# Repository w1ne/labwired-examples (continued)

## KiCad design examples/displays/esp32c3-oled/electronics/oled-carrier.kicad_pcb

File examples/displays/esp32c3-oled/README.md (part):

# ESP32-C3 OLED device — Rev A candidate 3

This package contains a USB-powered OLED counter, its routed carrier PCB, firmware, enclosure CAD, assembly instructions and verification evidence. A Seeed XIAO ESP32C3 drives an Adafruit 326 STEMMA QT display. The counter starts at **19:00:00 after every reset** and advances once per second. It has no real-time clock, time-setting control or saved time.

**Status: engineering assembly candidate.** The corrected model retains the native PCB populated side at +Z and uses world Y = −editor Y. All **12/12** fit and registration checks pass. All **18 native drilled pads** match their STEP axes with zero XY error. The glass/support clearance remains **1.277 mm**, with **0.85 mm** support arms and the unchanged **0.8 mm** minimum-wall gate. Both printed parts pass DFM and closed-mesh checks; all **41/41** assembly STEP solids are valid. A fresh independent check passes **39 ordered geometric stages** for all 41 source parts and all 13 helper controls. Hosted assembly-path acceptance and physical qualification remain open. No physical prototype has been built.

The previous source reconstructed the populated assembly in the PCB editor's downward-Y frame. Rotating only the bare substrate hid that reflection. Candidate 3 corrects the primitive geometry, connector frames, print orientations and exported files. The earlier candidate releases remain immutable. Studio revision 3 now stores this corrected source and its original native STEP asset. Its ready mesh is bound to the exact source, asset manifest and deployed producer in the [saved-revision receipt](cad/verification/studio-current/revision.json).

[Open the canonical Lab](https://app.labwired.com/?lab=esp32c3-oled-lab) · [Current Studio revision 3](https://app.kernelcad.com/p/t_IaE1EE?version=3) · [Track remaining work](https://github.com/w1ne/labwired/issues/3550)

The canonical Lab integration is delivered by the associated platform change. Until that change deploys, the public Lab can still show the previous Super Mini starter. This repository and the release files identify the candidate independently of deployment.

## Package contents

| File or folder | Use |
| --- | --- |
| [bom.csv](bom.csv) | Complete electronics and enclosure BOM, with scoped assembly references and quantities |
| [electronics/oled-carrier.kicad_pro](electronics/oled-carrier.kicad_pro) | Editable KiCad 10 project; keep the entire `electronics/` folder with its rules and libraries |
| [manufacturing/oled-carrier-fabrication.zip](manufacturing/oled-carrier-fabrication.zip) | Gerbers, plated/non-plated drills, drill maps and fabrication settings |
| [manufacturing/oled-carrier-schematic.pdf](manufacturing/oled-carrier-schematic.pdf) | Readable schematic |
| [firmware/platformio.ini](firmware/platformio.ini) | Pinned XIAO build and separate address-scanner environment |
| [firmware/release-manifest.json](firmware/release-manifest.json) | Exact public ELF, merged flash, startup snapshot and ROM identities |
| [labwired/circuit.json](labwired/circuit.json) | The actual functional starter diagram exported from the platform implementation |
| [cad/esp32c3-oled-enclosure.kcad.ts](cad/esp32c3-oled-enclosure.kcad.ts) | Editable, parameterized KernelCAD source |
| [cad/exports/](cad/exports/) | Assembly STEP and separate base/lid STEP, STL and 3MF files |
| [cad/assembly.txt](cad/assembly.txt) | Print orientation, hardware stack, assembly sequence and fit checks |
| [release-manifest.json](release-manifest.json) | Package identity and file integrity manifest |
| [verification/](verification/) | Observed firmware results, build provenance and reproducible checks |

The complete package includes the `.kicad_dru` fastener keepouts, local symbol/footprint libraries and mechanical component assets. The Lab's native viewer downloads the `.kicad_pcb`, `.kicad_sch` and `.kicad_pro` for inspection; use the complete package for editing or fabrication.

## Electrical design

The carrier is **70 × 45 × 1.6 mm**, with two copper layers and four 2.9 mm non-plated mounting holes. It contains two XIAO sockets, a JST SH cable connector and two 4.7 kΩ pull-ups. The XIAO and OLED are purchased modules; their internal boards are not part of the carrier Gerbers.

| Signal | Controller | Carrier connector | Display |
| --- | --- | --- | --- |
| SDA | D2 / GPIO4, J2.3 | J1.3 | STEMMA QT SDA |
| SCL | D3 / GPIO5, J2.4 | J1.4 | STEMMA QT SCL |
| Power | 3V3, J3.5 | J1.2 | STEMMA QT VCC |
| Ground | GND, J3.6 | J1.1 | STEMMA QT GND |

GPIO4/5 are explicit firmware assignments. The XIAO's usual D4/D5 I²C labels refer to different GPIOs. Use the table above.

Use the **Adafruit 326 STEMMA QT revision**. Close **SJ3 / ADDR** to select `0x3C`; its open/default address is `0x3D`. Keep the factory I²C jumpers SJ1/SJ2 closed. Leave the optional eight-pin JP2 header unpopulated. Its physical order is SDA, SCL, DC/SA0, RST, CS, regulated 3.3 V output, Vin and GND.

Use the specified **Samtec BHS-107-G-A / HSS-107-G-2 round-pin pair**. The module tails are 0.46 mm in diameter and fit the XIAO's native 0.85 mm holes. A 0.635 mm square post has a 0.898 mm diagonal and does not fit that hole specification. The nominal mated board gap is 9.77 mm. Substituting a generic header changes both fit and enclosure height.

USB supplies the device. Battery pads and the carrier's VBUS socket contact are unused. The demo does not enable Wi-Fi or Bluetooth; its supplied antenna remains separate. Install the antenna before using firmware that enables RF.

The Lab diagram represents the **MCU/display functional connections**. The native carrier and complete BOM also contain sockets, connectors, pull-ups and mounting features. The preserve import of the carrier is an identity/geometry result and has no runnable MCU model. The firmware tests do not simulate all carrier copper, cable parasitics, analog power or mechanical fit.

## Build and flash

Use PlatformIO Core **6.2.0**. The project pins `espressif32@7.0.1`, the official `seeed_xiao_esp32c3` board and Arduino. Run these commands from this directory:

```sh
pio run -d firmware -e clock
pio run -d firmware -e i2c_scan
```

Both environments were built successfully. The tested clock application uses **271,678 bytes of flash** and **15,140 bytes of RAM** in this toolchain. The unchanged workshop sketch is mirrored from core commit `941a6c5caf0c53b66aa5af9290e5ecba5972ec72`; [source-provenance.json](firmware/source-provenance.json) records its path and SHA256.

For initial assembly, connect a USB-C **data** cable with the lid removed. Select the actual serial port when more than one board is connected:

```sh
pio run -d firmware -e i2c_scan -t upload --upload-port /dev/ttyACM0
pio device monitor -d firmware -e i2c_scan --port /dev/ttyACM0
```

The scanner must report `I2C_ACK 0x3C`. Stop the monitor, then upload the clock:

```sh
pio run -d firmware -e clock -t upload --upload-port /dev/ttyACM0
pio device monitor -d firmware -e clock --port /dev/ttyACM0
```

Confirm visible changes and serial lines `WORKSHOP_TICK 19:00:00`, then `WORKSHOP_TICK 19:00:01`. If automatic USB download entry is unavailable, hold BOOT, press and release RESET, then release BOOT and retry upload. Keep both buttons accessible until bring-up is complete.

The public runtime is [firmware-demos-v19](https://github.com/w1ne/labwired-core/releases/tag/firmware-demos-v19). Its ELF, merged flash and startup snapshot are a matched set. The startup snapshot was captured through real ROM boot from those exact bytes. The separate package build uses the same sketch and has a different ELF hash. Project paths can change ELF bytes. No byte-identical rebuild claim is made.

[verification/reproduce.txt](verification/reproduce.txt) downloads and checks the public runtime and runs the existing LabWired CLI against the packaged configuration. It also describes the standalone-build ROM-boot check. The package does not add a simulator or a custom device model.

## Assemble the candidate

1. Follow [electronics/assembly-notes.txt](electronics/assembly-notes.txt). Populate the five carrier components, fit the round-pin headers and inspect every joint. Check the four signal continuities and absence of a 3V3/GND short before connecting USB.
2. Configure the OLED for `0x3C`. Connect the **Adafruit 4210 100 mm** STEMMA QT cable. Run the scanner and clock with the assembly open.
3. Print the base and lid from their separate exports. Use the orientations and starting PETG settings in [cad/assembly.txt](cad/assembly.txt). Print checks are geometric checks; no printed sample has been measured.
4. Install the four 5 mm carrier spacers, four 25 mm lid spacers, washers and exact screw lengths from the BOM. Mount the OLED to the removed lid with the specified M2 hardware and **Wera 2069 05118120001**4 mm nut driver (5.7 mm outer blade diameter). Route the cable through the documented service space.
5. Confirm all fit checks below before closing. The lid must seat without bowing, cable compression or load on the OLED glass.
6. Check USB insertion, clock updates, reset behavior and repeated lid removal. Record actual module revision, printed dimensions, cable identity and measured clearances in issue [#3550](https://github.com/w1ne/labwired/issues/3550).

### Open physical-fit checks

- **Glass/support clearance:** the two open supports beside the glass now provide **1.277 mm nominal clearance**. They retain the original M2 screw positions and **0.85 mm arms/back**. The measured lid minimum wall is **0.8498 mm**, above the unchanged **0.8 mm** limit. The old round supports fail the new 1.0 mm nominal clearance gate at 0.277 mm; the negative-control receipt is included. Measure the received OLED and print against the proposed 0.5 mm bench clearance target. This is not a tolerance-qualified physical fit.
- **Vertical glass clearance:** nominally 0.50 mm for the stated 1.80 mm glass/film envelope. Check the actual display and printed lid.
- **USB cable:** the CAD access check uses a 16 × 8 mm plug overmold. The selected cable vendor does not publish overmold dimensions. Check full connector engagement with the actual cable.
- **Cable and short spacer stack:** the flexible cable and mating plug bodies are not fit-verified. The nominal opposing screw-tip gap in the 5 mm spacers is 0.44 mm; verify clamping and absence of screw bottoming.
- **Module revision:** the current native XIAO board is 1.6 mm thick. The older vendor STEP uses 1.0 mm. The assembly records the adaptation and conservative component envelopes; inspect the purchased revision.

## Observed verification

| Check | Observed result | Scope |
| --- | --- | --- |
| KiCad **10.0.8** ERC | **0 violations** | Native schematic, recorded rule configuration |
| KiCad **10.0.8** DRC | **0 violations, 0 unconnected items, 0 parity issues** | Routed carrier; 39 tracks and 7 vias |
| Native preserve import | Exact SHA256 retained | Unattached board; no MCU simulation proof |
| Package-build ROM boot | **5/5 assertions pass**, 300 million steps | Banner, both tick strings, nonblank display region and bounded stop |
| Published runtime + packaged configuration | **5/5 assertions pass**, 300 million steps | Cold boot of exact v19 bytes with the exported Lab system |
| Published runtime + browser WASM | Two distinct nonblank 128×64 frames; **19:00:00 → 19:00:01** | Exact v19 ELF/flash/snapshot and pinned core engine |
| Enclosure solids and print orientations | **41/41 STEP solids valid; base/lid FDM pass; 16/16 fit, registration and tool-clearance requirements pass** | Corrected native-coordinate CAD and configured FDM geometry |
| Independent ordered path check | **39/39 stages pass; all 41 source parts covered** | Current-source continuous mesh/native swept-envelope evidence in [tool-access](cad/verification/tool-access/ordered-path-summary.json); required holds and a shifted-screw negative retained |
| Specified nut driver | **0.150 mm minimum nominal clearance at all four nuts** | Wera 05118120001,1.4 mm engagement,0.2 mm PCB tip gap;5.9 mm,6.2 mm and over-inserted negative controls |
| Hosted assembly-path acceptance | **Open** | Earlier budget/contact receipts remain; independent follow-up does not change the hosted result |
| `design_loop` review | **Pass: functional, quality and screenshot review** | Corrected source, exact native STEP and actual closed/interior/lid-print renders |
| Printed/device prototype | **Not performed** | Electrical measurements, cable fit and physical assembly remain open |

The native reports record four default ignored ERC categories and five default ignored DRC categories. There are no explicit DRC exclusions. See [manufacturing/validation.json](manufacturing/validation.json) for the complete settings and hashes.

The two frame hashes are identical between the separate package-build CLI run and the released-runtime browser WASM run. The complete CLI result is retained as `verification/package-rom-boot-result.json.gz`; the readable observations preserve its source hash. This evidence does not mint a hosted `model_verified` badge.

## Sources and licensing

Manufacturer geometry, datasheets and component attributions are recorded in [electronics/provenance.json](electronics/provenance.json), [hardware-interface.json](hardware-interface.json) and the CAD receipts. The editable carrier and example scripts carry the included [MIT notice](LICENSE). The mirrored firmware carries its original [MIT notice](firmware/LICENSE). KiCad-library and imported manufacturer assets retain their individual notices. Espressif ROM images remain Espressif copyright and are linked from the pinned core source; the example MIT license does not apply to them.

## Native coordinate registration

The electrical interface tables retain KiCad editor coordinates. The CAD uses (X, Y, Z) = (editorX, −editorY, Z up) and keeps the native substrate's +Z side. The imported substrate receives only a positive thickness scale and Z=8 mm translation. Authored primitives enter this frame before boolean construction; purchased fasteners retain rigid transforms.

[Native registration](cad/verification/handedness/native-registration.json) binds the exact PCB, STEP, portable source, submitted source and staged evaluation. It checks all 18 drilled pad centres and an ordered three-pad orientation witness. Three real clearance gauges pass at 0.200 mm; restoring the historical 180° substrate rotation fails all three. The prior [design loop](cad/verification/handedness/design-loop.json) and [print mesh check](cad/verification/handedness/mesh-export-check.json) remain evidence for the manufactured geometry. The tool-only follow-up adds four clearance requirements and a sourced driver; [exact 41-part geometry equivalence](cad/verification/tool-access/geometry-equivalence.json) confirms no manufactured part changed. The current [ordered path proof](cad/verification/tool-access/ordered-path-summary.json) identifies the updated source.

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
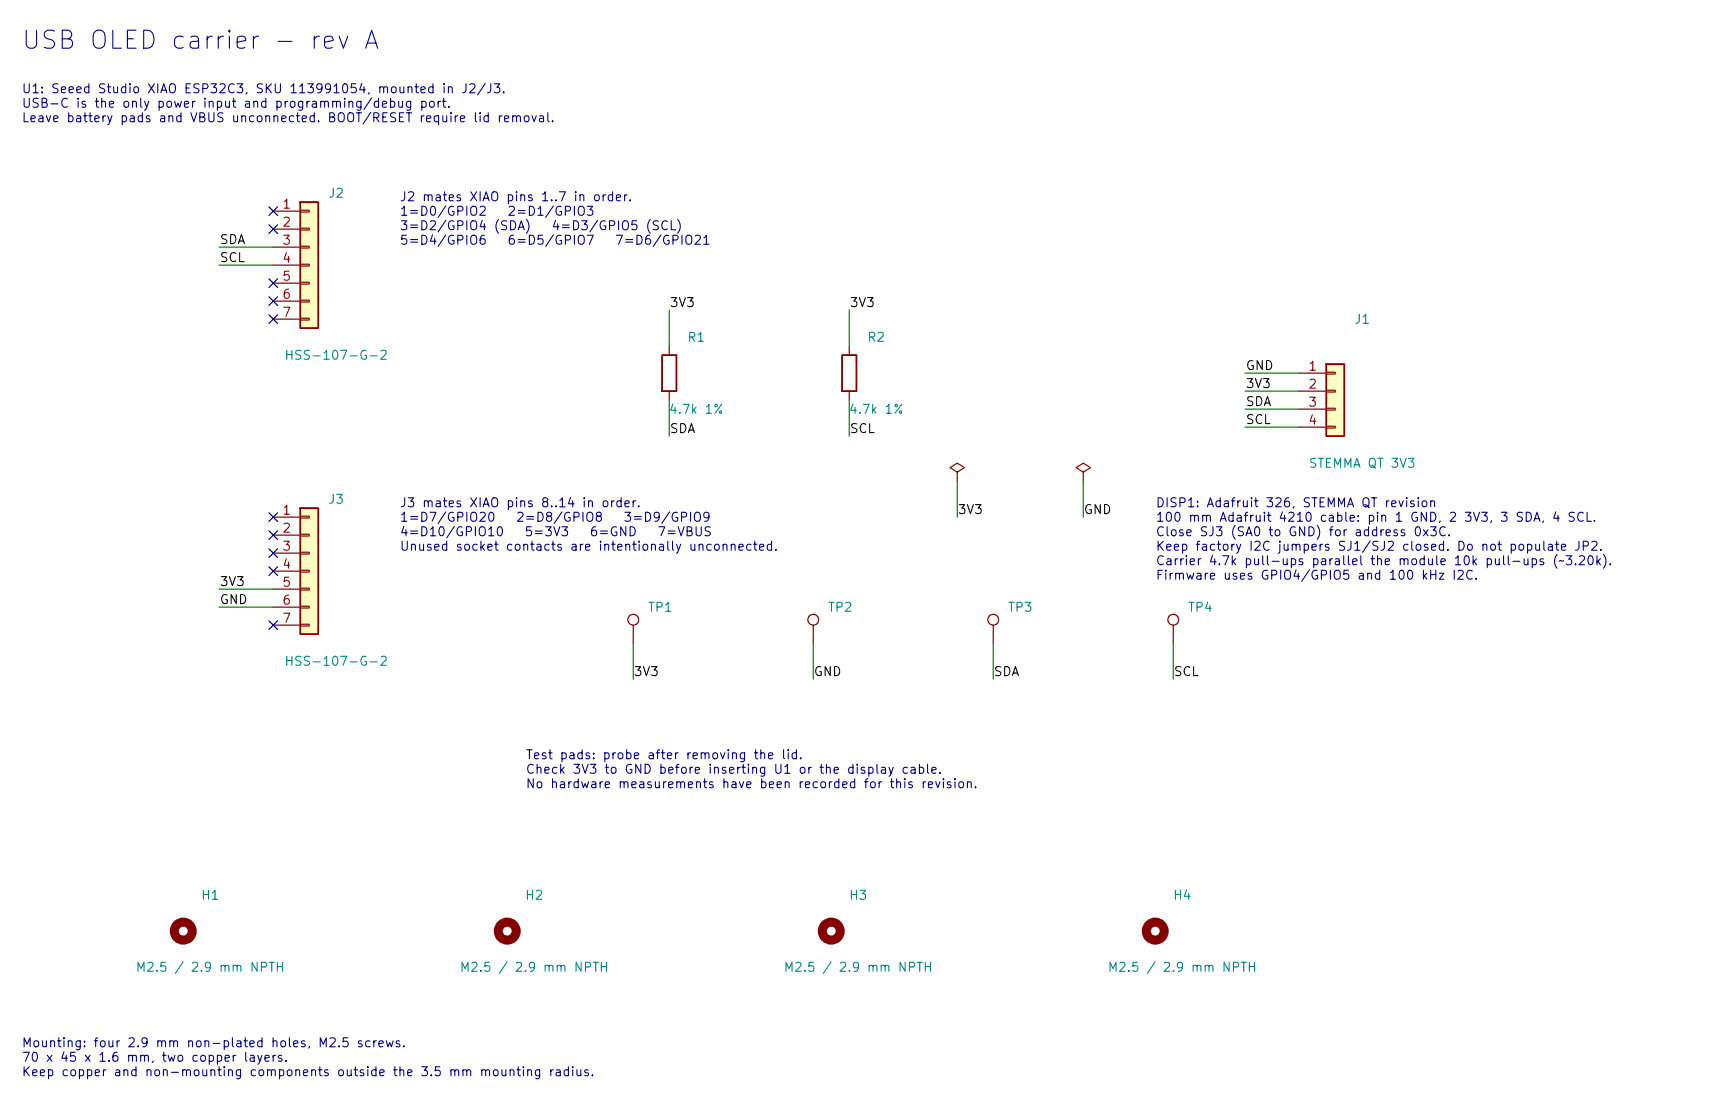
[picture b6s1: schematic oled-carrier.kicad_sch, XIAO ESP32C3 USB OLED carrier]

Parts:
H1, H2, H3, H4: M2.5 / 2.9 mm NPTH; MountingHole
J1: STEMMA QT 3V3; Display4; MPN SM04B-SRSS-TB(LF)(SN)
J2, J3: HSS-107-G-2; Socket7; MPN HSS-107-G-2
R1, R2: 4.7k 1%; R; MPN RC0603FR-074K7L
TP1: 3V3; TestPoint
TP2: GND; TestPoint
TP3: SDA; TestPoint
TP4: SCL; TestPoint

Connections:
/3V3: J1.2, J3.5, R1.1, R2.1, TP1.1
/GND: J1.1, J3.6, TP2.1
/SCL: J1.4, J2.4, R2.2, TP4.1
/SDA: J1.3, J2.3, R1.2, TP3.1

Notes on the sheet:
USB OLED carrier - rev A
U1: Seeed Studio XIAO ESP32C3, SKU 113991054, mounted in J2/J3. USB-C is the only power input and programming/debug port. Leave battery pads and VBUS unconnected. BOOT/RESET require lid removal.
J2 mates XIAO pins 1..7 in order. 1=D0/GPIO2 2=D1/GPIO3 3=D2/GPIO4 (SDA) 4=D3/GPIO5 (SCL) 5=D4/GPIO6 6=D5/GPIO7 7=D6/GPIO21
J3 mates XIAO pins 8..14 in order. 1=D7/GPIO20 2=D8/GPIO8 3=D9/GPIO9 4=D10/GPIO10 5=3V3 6=GND 7=VBUS Unused socket contacts are intentionally unconnected.
DISP1: Adafruit 326, STEMMA QT revision 100 mm Adafruit 4210 cable: pin 1 GND, 2 3V3, 3 SDA, 4 SCL. Close SJ3 (SA0 to GND) for address 0x3C. Keep factory I2C jumpers SJ1/SJ2 closed. Do not populate JP2. Carrier 4.7k pull-ups parallel the module 10k pull-ups (~3.20k). Firmware uses GPIO4/GPIO5 and 1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
Test pads: probe after removing the lid. Check 3V3 to GND before inserting U1 or the display cable. No hardware measurements have been recorded for this revision.
Mounting: four 2.9 mm non-plated holes, M2.5 screws. 70 x 45 x 1.6 mm, two copper layers. Keep copper and non-mounting components outside the 3.5 mm mounting radius.

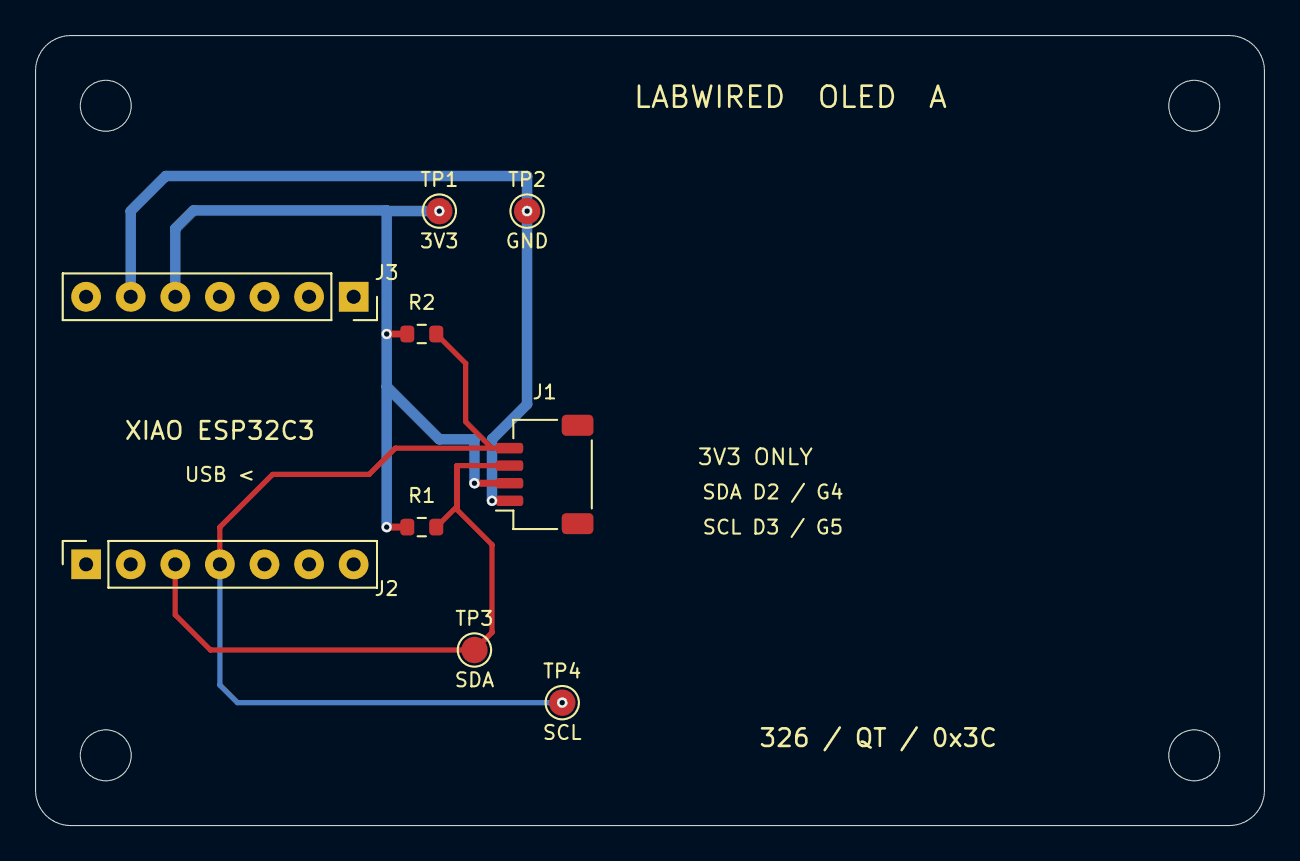
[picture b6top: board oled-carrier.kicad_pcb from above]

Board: 2 copper layers, 70.0 x 45.0 mm, 13 parts (0 on the bottom side), 4 nets.

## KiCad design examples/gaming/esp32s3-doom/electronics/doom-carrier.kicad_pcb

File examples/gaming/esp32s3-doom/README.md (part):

# ESP32-S3 Doom desktop device — revision A

This package supplies an editable KiCad 10 carrier, manufacturing outputs, physical ESP-IDF firmware, a fitted desktop enclosure, an exact bill of materials, and retained validation evidence. It targets **ESP32-S3-DevKitC-1-N16R8 PCB v1.0** and **LCDWiki MRB3205**. It is a release candidate. Hardware current, temperature, cable dress and printed fit remain unmeasured; see [the acceptance record](validation/acceptance.json) and [issue #3552](https://github.com/w1ne/labwired/issues/3552).

## What the device does

The ESP32-S3 runs the Doom engine from flash and an 8 MB octal PSRAM. An ILI9341 panel receives a 16-bit 8080 bus through the chip's LCD_CAM/GDMA hardware. The display is 320 × 240; Doom uses a 320 × 200 image with a 20-pixel border above and below. A PC terminal connected to the board's UART USB socket supplies keyboard input. The carrier does not include dedicated game buttons, audio, a battery, touch input or an SD card.

The fresh physical firmware has booted from the real mask ROM in LabWired and produced the title screen on the existing I80 panel model. The captured image is a framebuffer dump, not a mock-up. A simulated frame rate is not a physical-device benchmark.

## Package contents

| Directory or file | Purpose |
|---|---|
| `electronics/doom-carrier.kicad_pro` | Native KiCad project, local symbol/footprint libraries and design rules |
| `electronics/doom-carrier.kicad_sch` | Complete carrier schematic |
| `electronics/doom-carrier.kicad_pcb` | Routed 80 × 100 × 1.6 mm carrier, two copper layers |
| `manufacturing/` | Gerbers, plated/non-plated drills, assembly positions, netlist and PDF drawings |
| `bom.csv` | Exact ordering codes and quantities, including case hardware |
| `connector-map.csv` | All 34 display connector positions and their signal destinations |
| `firmware/source/` | Complete GPL-2.0 Doom/ESP-IDF application source |
| `firmware/build.sh` | Digest-pinned ESP-IDF container build and complete-flash assembly |
| `firmware/artifacts/` | ELF, application, bootloader, partition table, full flash image and checksums |
| `mechanical/doom-desktop.kcad.ts` | Editable source for the assembly, base, lid and ribbon depth spacer |
| `mechanical/*.step` | Neutral CAD exports |
| `mechanical/*-print.stl`, `*-print.3mf` | Millimetre print exports in their intended print orientations |
| `validation/` | Electrical, mechanical, build and simulation receipts, plus real renders |
| `release-manifest.json` | File inventory, hashes, declared scope and release state |

## Exact hardware contract

Use the listed PCB v1.0 DevKit. That revision routes its RGB LED to GPIO48. PCB v1.1 changes the LED route to GPIO38, which this package uses for LCD reset. A board sold under a similar name is not sufficient evidence of compatibility. Check the revision marking and component layout before insertion. The firmware clears the v1.0 RGB LED at startup and does not enable the radio.

Use MRB3205, the **34-pin, 16-bit** module. Set R16 to 0 Ω and leave R8 open. The carrier supplies 3.3 V; close the display module's J1 bypass as specified by its schematic. Do not substitute the visually similar SPI, 8-bit or 40-pin products.

| Signal | ESP32-S3 GPIO | MRB3205 pin |
|---|---:|---:|
| D0…D15 | 1…16, in the same order | 6…21 |
| WR | 17 | 3 |
| DC/RS | 18 | 2 |
| CS | 21 | 1 |
| RST | 38 | 5 |
| BL | 39 | 23 |
| RD | 10 kΩ pull-up to 3.3 V | 4 |
| VDD | 3.3 V | 24, 25 |
| GND | Ground | 26, 27 |

Each of the 21 MCU-driven data/control signals has its own 33 Ω source resistor. The three unused SD/flash/touch chip selects have separate 10 kΩ pull-ups. NC, MISO, MOSI, PEN and CLK are unconnected because their associated functions are not used. GPIO26…37 are reserved for the N16R8 memory configuration. GPIO3 is a strapping pin; the selected LCD data input does not add an external pull-up or pull-down to it.

The ribbon cable is **IDSD-17-D-04.00-G**, straight 1:1, with no reverse-wiring suffix. Pin 1 is marked on the carrier and identified by the cable's red edge. Check continuity from carrier J3.1 to display pin 1 before power. Do not infer pin numbers from the direction the cable exits its housing.

## Power

Connect the Adafruit 592 data cable to the DevKit's **UART** Micro-USB connector. It powers the board and carries programming, logs and keyboard input. The carrier takes 3.3 V from the DevKit. The factory v1.0 schematic identifies the SGM2212-3.3 regulator; the manufacturer rates that regulator for 800 mA, subject to thermal conditions. This is a component rating, not a measured allowance for the finished device. The display manual leaves its power consumption unspecified.

Before physical acceptance, measure total current and 3.3 V at TP1/TP2 during startup, a fully lit screen and continuous gameplay. Check regulator temperature with the case closed. Record supply/cable, ambient temperature, current, rail minimum and test duration. Do not add another supply to the 3.3 V rail while USB powers the board. Full-backlight current and thermal margin are open items in issue #3552.

## Manufacture and assemble

1. Manufacture the carrier from the supplied Gerbers and drill files. Use the native 1.6 mm, two-layer design. The routed board contains 38 footprints: 30 populated electrical components, four mounting holes and four test pads. Check the schematic and BOM together before assembly.
2. Populate the 25 resistors and two capacitors. C1 is the TDK 10 µF X7R part; C2 is the TDK 100 nF X8R part. Solder the two 22-way sockets and the 34-way display header. Keep them perpendicular to the board. Inspect every joint and check that 3.3 V is not shorted to ground.
3. Print the base and lid in PETG with a 0.4 mm nozzle, 0.2 mm layers and four perimeters. The exports already place each part on its print face. The USB aperture has a 45° roof and a 6 mm top bridge. Inspect the four nut pockets and registration tabs; remove debris before inserting hardware. These settings define the candidate process and have not been physically qualified.
4. Print the ribbon depth spacer with 0.1 mm layers. Its nominal thickness is 1.1 mm. Measure the display header's exposed pin length and subtract the measured spacer thickness: the result must be **5.59–6.22 mm**. The drawing's nominal 7.0 mm pins and the 1.1 mm spacer give 5.9 mm insertion. Change the single `ribbonSpacerT` constant in the editable source when the measured stack requires it; regenerate and validate the export. Never force the socket against its internal stop.
5. Insert four M3 nuts into the base's inward-facing pockets while the base is empty. Fit the four 7 mm Harwin standoffs over 0.5 mm nylon washers. Retain them from below with M2.5 × 5 mm countersunk screws. Fit the carrier with four M2.5 × 5 mm cap screws. The lower and upper screws do not meet inside the 7 mm through-threaded standoffs.
6. Insert the exact DevKit with its USB edge toward the case's rear aperture. Align all 44 pins before applying even pressure. Keep the antenna region free of added metal and wiring. The PCB includes a copper keep-out; RF performance is not qualified.
7. Assemble the display and lid on the bench. Put a 4 mm nylon spacer at each display mounting hole between the PCB front and lid underside. Use M2.5 × 12 mm screws through the lid, with nylon washers and M2.5 nuts behind the display PCB. Hold the nuts with a 5 mm tool. Support the module at its PCB, not the glass. Tighten only enough to retain it; the candidate contains no measured torque specification.
8. Put the printed depth spacer over the display header and mate the display-end IDC socket against it. Mate the other socket to carrier J3. Confirm the red-edge/pin-1 continuity. Support the lid separately while open. Dress the ribbon in the open bay without a sharp crease, pinching it under a screw boss, or loading either connector. The cable's exact flex shape is not represented as a rigid CAD solid.
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
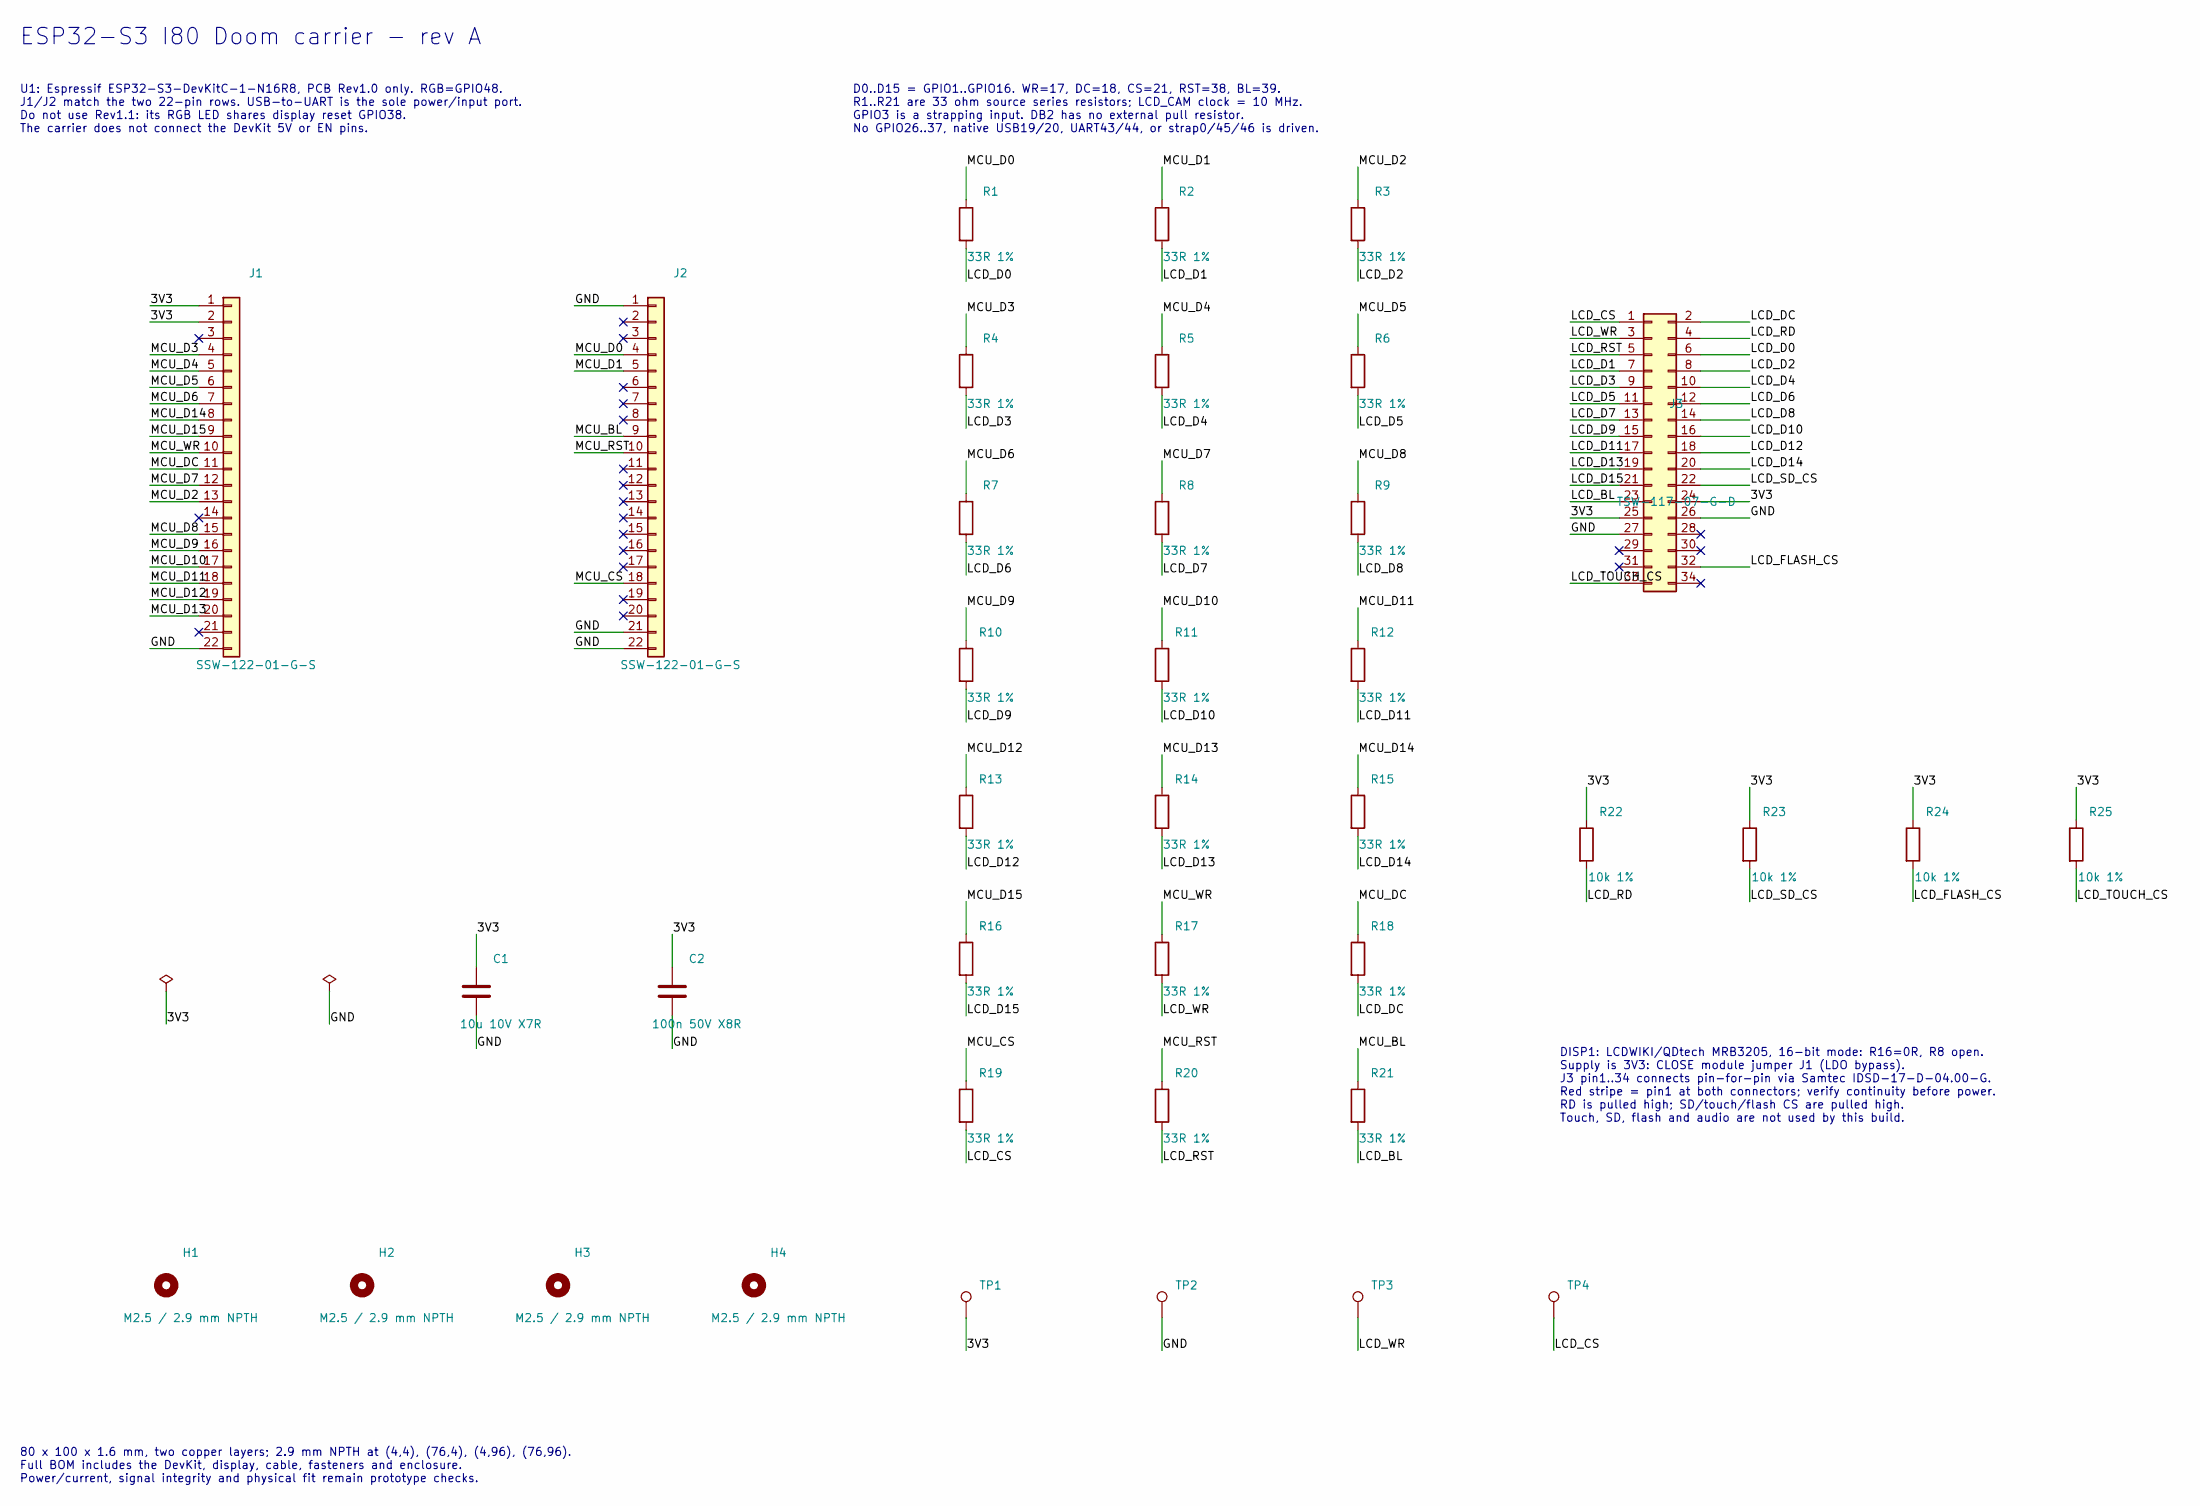
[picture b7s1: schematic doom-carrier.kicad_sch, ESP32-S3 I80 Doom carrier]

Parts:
C1: 10u 10V X7R; C; MPN C2012X7R1A106K125AC
C2: 100n 50V X8R; C; MPN C2012X8R1H104K125AA
H1, H2, H3, H4: M2.5 / 2.9 mm NPTH; MountingHole
J1, J2: SSW-122-01-G-S; Socket22; MPN SSW-122-01-G-S
J3: TSW-117-07-G-D; Display34; MPN TSW-117-07-G-D
R1, R2, R3, R4, R5, R6, R7, R8, R9, R10, R11, R12, R13, R14, R15, R16, R17, R18, R19, R20, R21: 33R 1%; R; MPN RC0603FR-0733RL
R22, R23, R24, R25: 10k 1%; R; MPN RC0603FR-0710KL
TP1: 3V3; TestPoint
TP2: GND; TestPoint
TP3: LCD_WR; TestPoint
TP4: LCD_CS; TestPoint

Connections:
/3V3: C1.1, C2.1, J1.1, J1.2, J3.24, J3.25, R22.1, R23.1, R24.1, R25.1, TP1.1
/GND: C1.2, C2.2, J1.22, J2.1, J2.21, J2.22, J3.26, J3.27, TP2.1
/LCD_BL: J3.23, R21.2
/LCD_CS: J3.1, R19.2, TP4.1
/LCD_D0: J3.6, R1.2
/LCD_D1: J3.7, R2.2
/LCD_D2: J3.8, R3.2
/LCD_D3: J3.9, R4.2
/LCD_D4: J3.10, R5.2
/LCD_D5: J3.11, R6.2
/LCD_D6: J3.12, R7.2
/LCD_D7: J3.13, R8.2
/LCD_D8: J3.14, R9.2
/LCD_D9: J3.15, R10.2
/LCD_D10: J3.16, R11.2
/LCD_D11: J3.17, R12.2
/LCD_D12: J3.18, R13.2
/LCD_D13: J3.19, R14.2
/LCD_D14: J3.20, R15.2
/LCD_D15: J3.21, R16.2
/LCD_DC: J3.2, R18.2
/LCD_FLASH_CS: J3.32, R24.2
/LCD_RD: J3.4, R22.2
/LCD_RST: J3.5, R20.2
/LCD_SD_CS: J3.22, R23.2
/LCD_TOUCH_CS: J3.33, R25.2
/LCD_WR: J3.3, R17.2, TP3.1
/MCU_BL: J2.9, R21.1
/MCU_CS: J2.18, R19.1
/MCU_D0: J2.4, R1.1
/MCU_D1: J2.5, R2.1
/MCU_D2: J1.13, R3.1
/MCU_D3: J1.4, R4.1
/MCU_D4: J1.5, R5.1
/MCU_D5: J1.6, R6.1
/MCU_D6: J1.7, R7.1
/MCU_D7: J1.12, R8.1
/MCU_D8: J1.15, R9.1
/MCU_D9: J1.16, R10.1
/MCU_D10: J1.17, R11.1
/MCU_D11: J1.18, R12.1
/MCU_D12: J1.19, R13.1
/MCU_D13: J1.20, R14.1
/MCU_D14: J1.8, R15.1
/MCU_D15: J1.9, R16.1
/MCU_DC: J1.11, R18.1
/MCU_RST: J2.10, R20.1
/MCU_WR: J1.10, R17.1

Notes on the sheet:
ESP32-S3 I80 Doom carrier - rev A
U1: Espressif ESP32-S3-DevKitC-1-N16R8, PCB Rev1.0 only. RGB=GPIO48. J1/J2 match the two 22-pin rows. USB-to-UART is the sole power/input port. Do not use Rev1.1: its RGB LED shares display reset GPIO38. The carrier does not connect the DevKit 5V or EN pins.
D0..D15 = GPIO1..GPIO16. WR=17, DC=18, CS=21, RST=38, BL=39. R1..R21 are 33 ohm source series resistors; LCD_CAM clock = 10 MHz. GPIO3 is a strapping input. DB2 has no external pull resistor. No GPIO26..37, native USB19/20, UART43/44, or strap0/45/46 is driven.
DISP1: LCDWIKI/QDtech MRB3205, 16-bit mode: R16=0R, R8 open. Supply is 3V3: CLOSE module jumper J1 (LDO bypass). J3 pin1..34 connects pin-for-pin via Samtec IDSD-17-D-04.00-G. Red stripe = pin1 at both connectors; verify continuity before power. RD is pulled high; SD/touch/flash CS are pulled high.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
80 x 100 x 1.6 mm, two copper layers; 2.9 mm NPTH at (4,4), (76,4), (4,96), (76,96). Full BOM includes the DevKit, display, cable, fasteners and enclosure. Power/current, signal integrity and physical fit remain prototype checks.

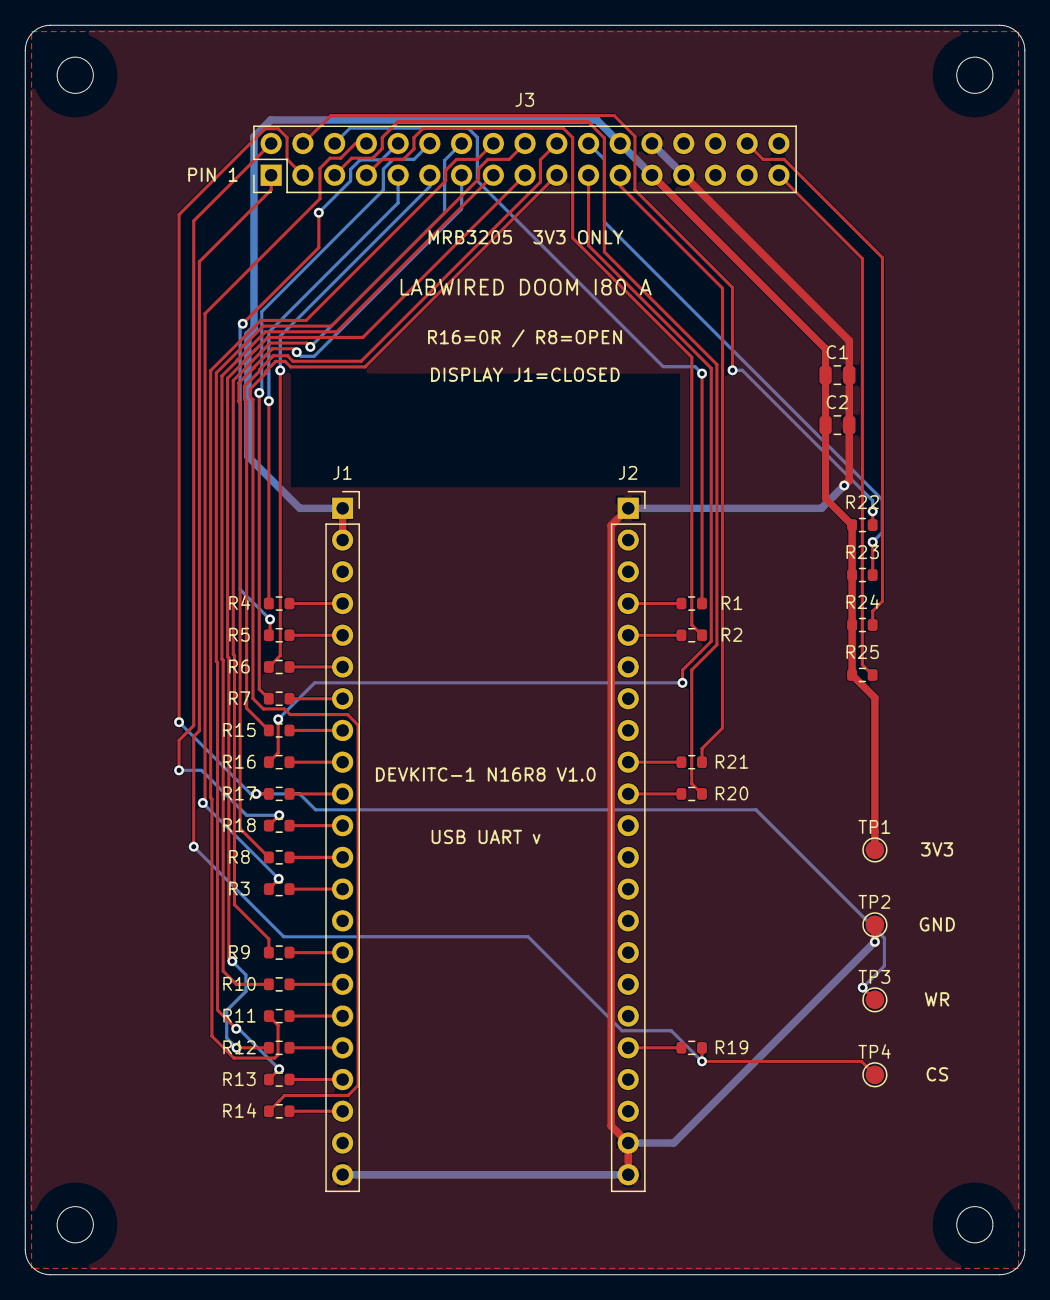
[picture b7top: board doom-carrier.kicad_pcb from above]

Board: 2 copper layers, 80.0 x 100.0 mm, 38 parts (0 on the bottom side), 48 nets.

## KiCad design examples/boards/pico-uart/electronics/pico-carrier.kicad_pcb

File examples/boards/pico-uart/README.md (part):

# Raspberry Pi Pico UART fixture — revision B candidate

This package turns the featured Pico example into a buildable USB-powered bench fixture. It contains a routed 60 × 70 mm carrier, a Raspberry Pi Pico SC0915 with specified Samtec headers, a fitted two-piece case, bootable Arduino Mbed firmware, a bill of materials, fabrication files, and verification receipts.

[Canonical LabWired project](https://app.labwired.com/?lab=rp2040-pico) · [Acceptance issue #3553](https://github.com/w1ne/labwired/issues/3553) · [Featured-project tracker #3547](https://github.com/w1ne/labwired/issues/3547)

The firmware prints the boot banner and toggles the Pico's actual GP25 LED. The console is UART0 on GP0/GP1 at 115200 baud, 8 data bits, no parity, one stop bit. The physical console uses an Adafruit 954 USB-to-TTL adapter. The Pico's micro-USB port supplies power and accepts the UF2 image.

## Runtime configuration

The package owns its runtime descriptor at `runtime/system.yaml`. It selects the existing RP2040 chip model, declares the 125,000,000 Hz model time base and UART0 console, and retains the active-high GP25 LED. `runtime/acceptance.yaml` references the exact hosted release ELF and the same five serial/GPIO acceptance clauses. Run it from this package with:

```sh
labwired test --script runtime/acceptance.yaml --no-uart-stdout --output-dir build/runtime-check
```

The exact released ELF passes all five clauses with this descriptor; `validation/explicit-runtime-acceptance.json` binds the source and result hashes. This model time base does not certify physical baud error or PLL behavior.

## Qualification

| Check | Recorded result | Evidence |
| --- | --- | --- |
| Native KiCad 10.0.8 schematic | 0 ERC violations | [ERC report](validation/erc.json) |
| Routed two-layer board | 0 DRC violations, 0 unconnected items, 0 schematic-parity issues | [DRC report](validation/drc.json) |
| Independent hosted native validation | Exact bytes preserved; KiCad10.0.8 reports0 errors and0 warnings | [Hosted DRC](validation/native-import-validation.json) |
| Released hosted firmware | All 5 oracle clauses passed; GP0 made 181 transitions and GP25 made 2 transitions before the gate stopped | [Model-verification receipt](validation/firmware-model-verify.json) |
| Local pinned SDK build | Build succeeded; the same 5 behavior assertions passed over 50,000,000 interpreted steps | [Local build acceptance](validation/local-build-acceptance.json) |
| Nominal fit and registration | All 12 requirements pass: five physical fit checks and seven native orientation checks | [Current evaluation](validation/handedness/evaluation.json) |
| Design review | Accepted: functional and quality checks passed, seven visual checks recorded; one source-count style heuristic explicitly reviewed | [Current design loop](validation/handedness/design-loop.json) |
| Assembly STEP | Export passed; all 50 re-imported solids are valid | [Current STEP inspection](validation/handedness/assembly-step-inspection.json) |
| Printed parts | Base/lid DFM pass; both STL and 3MF meshes have zero non-two-manifold edges and the declared dimensions | [Mesh check](validation/handedness/mesh-export-check.json), [base DFM](validation/handedness/base-dfm-verification.json), [lid DFM](validation/handedness/lid-dfm-verification.json) |
| Ordered geometric removal | 31/31 stages cover all 50 source parts; 494 intact-module/obstacle pairs pass conservative native sweeps; seven helper controls and an actual shifted-screw collision negative pass | [Source-bound result](validation/handedness/path/pico-ordered-complete-native-path.json), [provenance](validation/handedness/path/provenance.json) |
| Hosted assembly-path acceptance | The complete-scene and intact-module mesh computations exhausted their work budgets; both remain inconclusive | [Original result](validation/assembly-path-budget.json), [module budget result](validation/handedness/path/module-mesh-budget.json) |
| Physical qualification | No fabricated board, printed case, cable measurement, powered test, or assembly test has been recorded | [Bring-up procedure](ASSEMBLY.md) |

Model verification proves the listed behavior in the RP2040 model. The model assumes an ideal supply and derives time from a 125 MHz clock without tracking PLL reconfiguration. The oracle therefore checks serial content and pad transitions; it does not certify physical baud error, LED frequency, USB enumeration, power-on reset, or brown-out behavior.

## Package contents

- [Native KiCad project](electronics/pico-carrier.kicad_pro), [schematic](electronics/pico-carrier.kicad_sch), [routed PCB](electronics/pico-carrier.kicad_pcb), and project-local symbol/footprint libraries.
- [Readable schematic PDF](manufacturing/pico-carrier-schematic.pdf), [fabrication ZIP](manufacturing/pico-carrier-fabrication.zip), and [fabrication settings](manufacturing/fabrication-settings.json).
- [Full bill of materials](bom.csv), [electronic parts](electronics-bom.csv), and [mechanical/electrical interface](hardware-interface.json).
- [Editable enclosure source](mechanical/pico-uart-fixture.kcad.ts), [assembly STEP](mechanical/pico-uart-fixture.step), [base STL](mechanical/pico-uart-base.stl), and [lid STL](mechanical/pico-uart-lid.stl).
- [Arduino source](firmware/src/main.ino), [pinned build configuration](firmware/platformio.ini), [ELF](firmware/artifacts/pico-uart.elf), [UF2](firmware/artifacts/pico-uart.uf2), and [build manifest](firmware/release-manifest.json).
- [Assembly and bring-up instructions](ASSEMBLY.md), [source notices](THIRD_PARTY_NOTICES.txt), and [release hashes](SHA256SUMS).

## Electrical contract

Use the plain Raspberry Pi Pico SC0915. Solder two Samtec TSW-120-07-G-S headers into it. The specified Samtec SSW-120-01-G-S sockets establish an 11.05 mm nominal gap between the carrier's upper surface and the Pico PCB underside. A factory-header Pico H has an unspecified header stack in this package; its firmware is compatible, but its mechanical fit is not the released stack.

The carrier routes three nets: GND, UART_TX_GP0, and UART_RX_GP1. It does not distribute VBUS, VSYS, or 3V3. Power the Pico through its micro-USB connector. Leave the adapter's red 5 V lead disconnected and insulated.

| Carrier contact | Pico contact | Signal | Adafruit 954 lead |
| --- | --- | --- | --- |
| J3 pin 1 | GND through J1/J2 | Common reference | Black, GND |
| J3 pin 2 | Physical pin 1, GP0 | Pico UART0 TX | White, adapter RX |
| J3 pin 3 | Physical pin 2, GP1 | Pico UART0 RX | Green, adapter TX |
| No carrier contact | No connection | Adapter 5 V | Red: disconnected |

J3 pin 1 is the square pad. With USB at the top of the carrier, its contacts run downwards: GND, TX, RX. The pin numbers in the native schematic and PCB are authoritative.

J1 pins 1–20 mate Pico physical pins 1–20. J2 pins 1–20 mate Pico physical pins 40–21 in reverse numerical order. Both carrier socket pin-1 ends face the USB end. The connected grounds are J1 pins 3/8/13/18 and J2 pins 3/8/13/18; J2 pin 8 is Pico AGND. All other socket contacts are intentionally isolated. TP1 is GND, TP2 is TX, and TP3 is RX.

The released firmware transmits on GP0. GP1 is routed and available for later firmware; the present oracle does not claim a receive/echo test.

## Firmware

The released ELF SHA-256 is:

324a84cbb18276a4814bc4ecf7a20c8b7117ebe874d0df86952ea029dc84bce3

It was compiled by the existing hosted rpi-pico Arduino profile. Its image contains the RP2040 second-stage bootloader at 0x10000000 and the application after the 256-byte boot2 area. The UF2 is converted from this exact ELF for the RP2040 family.

This fixes a material packaging gap in the old simulator-only smoke program. That regression fixture remains in labwired-core as a baseline. This package uses the SDK's real clock, UART, GPIO and boot setup and operates GP25 through the Pico board definition.

To rebuild locally, install PlatformIO Core 6.2.0 and run from this package directory:

```sh
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
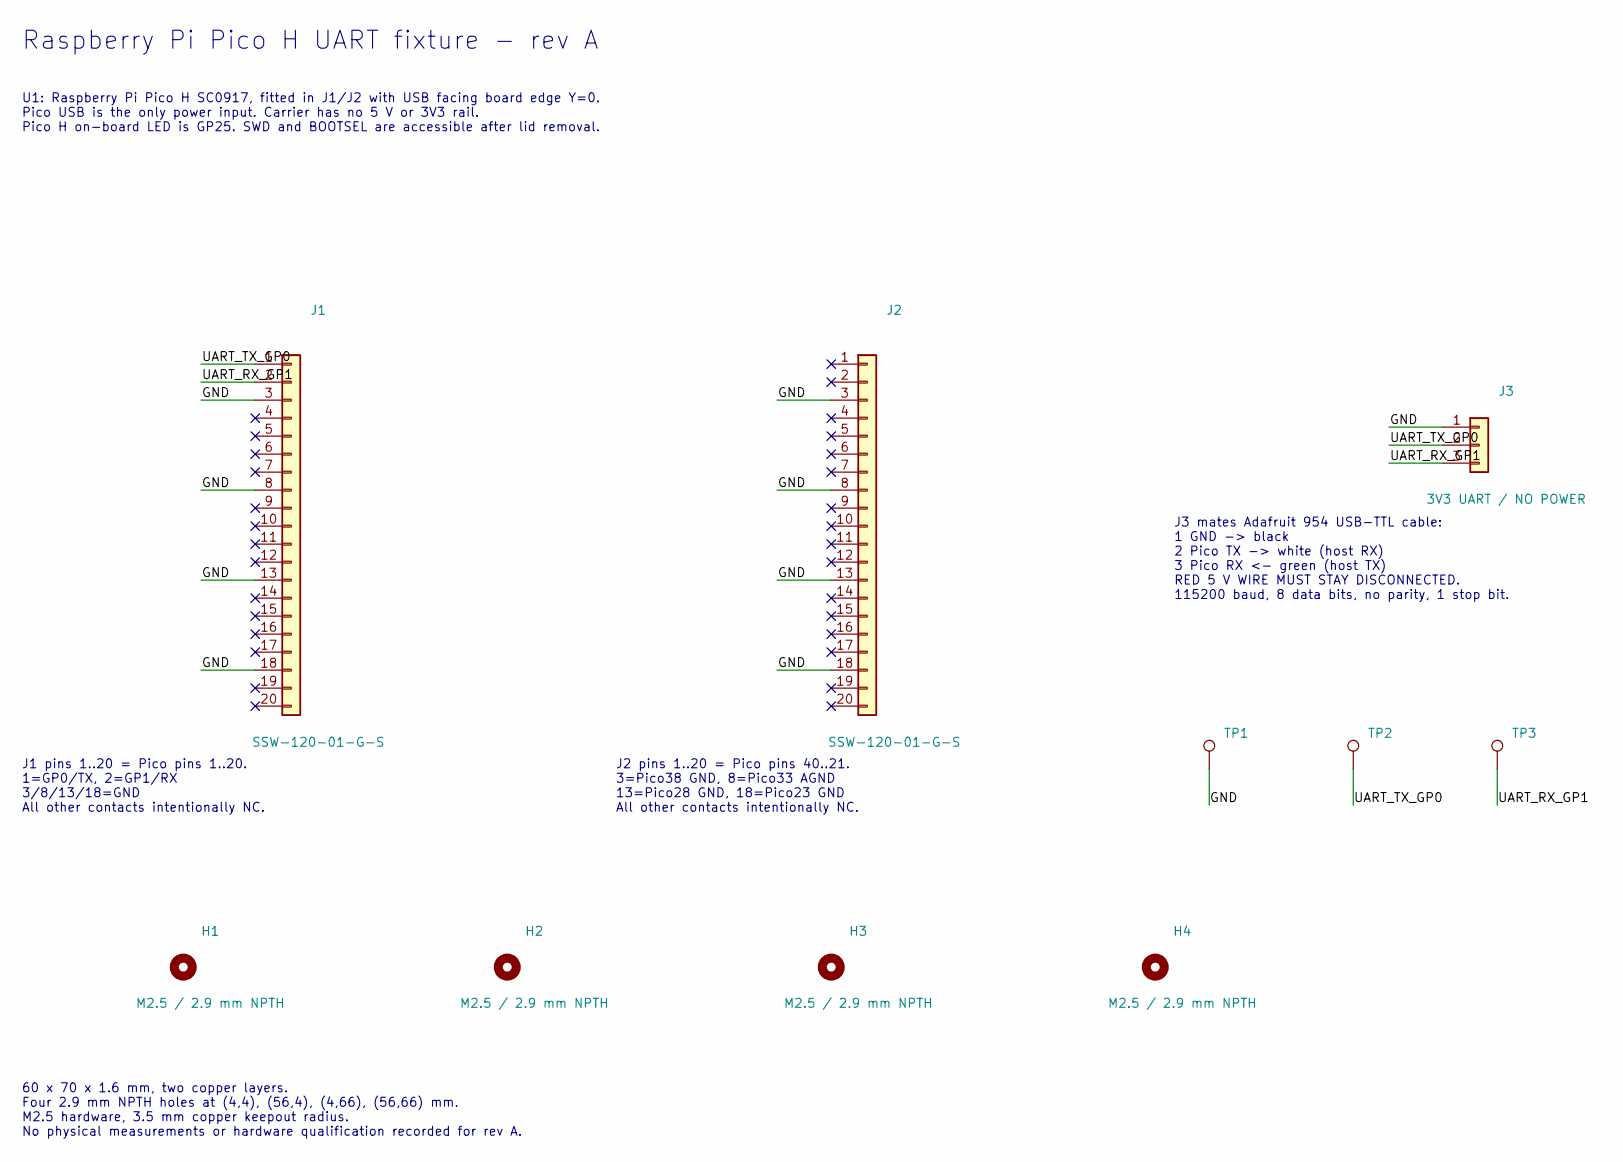
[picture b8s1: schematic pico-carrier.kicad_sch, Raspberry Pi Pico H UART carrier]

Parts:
H1, H2, H3, H4: M2.5 / 2.9 mm NPTH; MountingHole
J1, J2: SSW-120-01-G-S; Socket20; MPN SSW-120-01-G-S
J3: 3V3 UART / NO POWER; Console3; MPN TSW-103-07-G-S
TP1: GND; TestPoint
TP2: UART_TX_GP0; TestPoint
TP3: UART_RX_GP1; TestPoint

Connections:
/GND: J1.3, J1.8, J1.13, J1.18, J2.3, J2.8, J2.13, J2.18, J3.1, TP1.1
/UART_RX_GP1: J1.2, J3.3, TP3.1
/UART_TX_GP0: J1.1, J3.2, TP2.1

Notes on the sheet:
Raspberry Pi Pico H UART fixture - rev A
U1: Raspberry Pi Pico H SC0917, fitted in J1/J2 with USB facing board edge Y=0. Pico USB is the only power input. Carrier has no 5 V or 3V3 rail. Pico H on-board LED is GP25. SWD and BOOTSEL are accessible after lid removal.
J1 pins 1..20 = Pico pins 1..20. 1=GP0/TX, 2=GP1/RX 3/8/13/18=GND All other contacts intentionally NC.
J2 pins 1..20 = Pico pins 40..21. 3=Pico38 GND, 8=Pico33 AGND 13=Pico28 GND, 18=Pico23 GND All other contacts intentionally NC.
J3 mates Adafruit 954 USB-TTL cable: 1 GND -> black 2 Pico TX -> white (host RX) 3 Pico RX <- green (host TX) RED 5 V WIRE MUST STAY DISCONNECTED. 115200 baud, 8 data bits, no parity, 1 stop bit.
60 x 70 x 1.6 mm, two copper layers. Four 2.9 mm NPTH holes at (4,4), (56,4), (4,66), (56,66) mm. M2.5 hardware, 3.5 mm copper keepout radius. No physical measurements or hardware qualification recorded for rev A.

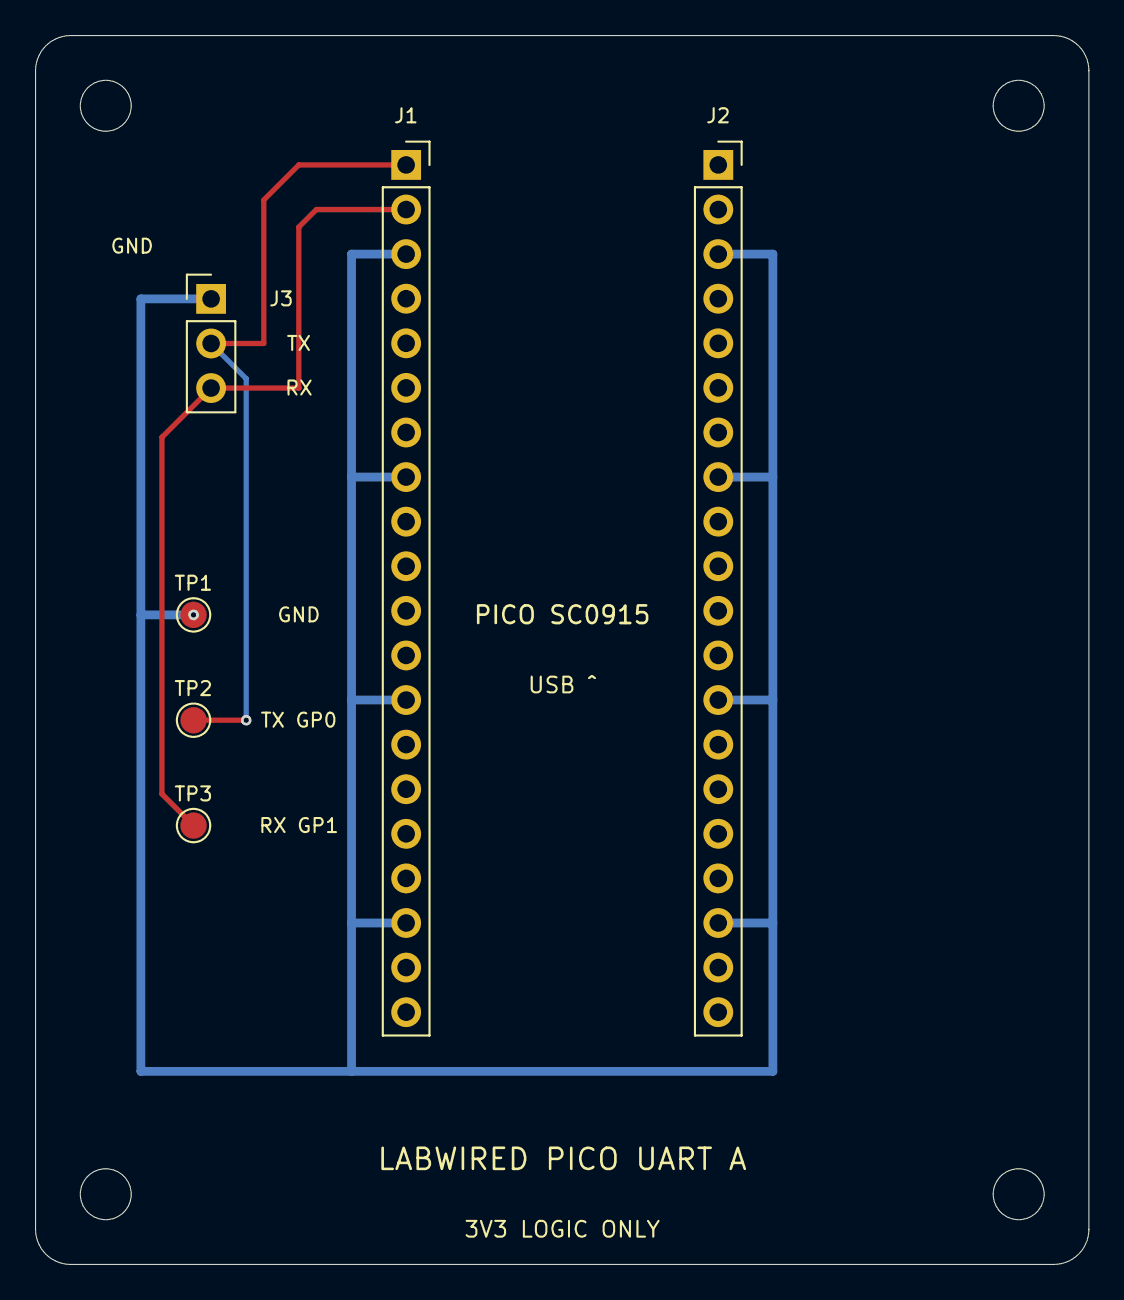
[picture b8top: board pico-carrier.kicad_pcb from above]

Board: 2 copper layers, 60.0 x 70.0 mm, 10 parts (0 on the bottom side), 3 nets.
